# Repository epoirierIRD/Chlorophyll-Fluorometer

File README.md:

<details>
<summary>⚠️ <strong>Latest News & Important Warnings</strong></summary>

### 📰 Latest News
- **06-05-2026:** Fluorometer has been successfully replicated by Jose Lopez ("pepe Tonio") in La Paz, Mexico during PSF Tempo workshop: Arturo, F. Colas, J. Flye Ste Marie, M. Gomez, E. Kraffe, R Martinez Riccon, M. Perez,  E. Poirier
- **30-04-2026:** Original PVC casing now replaced by 90mm diameter acrylic transparent casing
- **06-02-2026:** Branch https://github.com/epoirierIRD/Chlorophyll-Fluorometer/tree/main is ahead original
repository https://github.com/EnssatPhotonicsProjects/Chlorophyll-Fluorometer (not maintained)
- **14-12-2025:** Fluorometer has been successfully replicated by E. Poirier based on this repo.

### 🚨 Warnings
- This project is a student based innovation. It is now under development in research institutes, replicate with caution
- The fluorometer has not yet been validated in situ for Chla measurements. It has proven great results in laboratory under artifical light but not validated in situ
- It is not recommended to build it to have accurate measures of Chl a in situ

### ✅ Recommended Actions
- Report issues if you encounter mistakes, errors, lacks, etc... in this documentation

> ⚠️ **Disclaimer**
>
> This project is provided **as-is** for research and development purposes only.
> The authors make no guarantees regarding correctness, reliability, or fitness for any particular application.
> Use of this DIY instrument is entirely **at your own risk**.
</details>

# Chlorophyll-Fluorometer

## Description

This project aims to develop a portable and low-cost fluorometer for detecting chlorophyll-a concentration,
 a key indicator of phytoplankton presence. The project is conducted by students in photonics from Enssat in
  collaboration with the European Institute for Marine Studies (IUEM) and is part of an open-source initiative 
  to facilitate easy and cost-effective replication of the device.

This GitHub repository contains all the necessary resources and instructions for making the device.

The document [Fluoremeter overview](Fluorometer_overview.pdf) aims to provide an overview of the technical aspects of our fluorometer.

## Features

- Measures chlorophyll-a concentration in the range of [1-50] µg/L.
- Low-cost (approximately $200), low-tech, and open-source design.
- Portable

## Principle of fluorometry

The principle of fluorometry is based on the fact that chlorophyll-a in phytoplankton, when excited by a blue light source at
 a wavelength of 430 nm, re-emits light in the red spectrum around 670 nm. This red fluorescence is detected by a photodetector, 
 enabling the measurement of chlorophyll-a concentration in the sample.

## Functionality

With our setup, high sensitivity is achieved by usind two LEDs and a large-area photodiode to collect more efficiently fluorescence. 
A red filter is used to prevent the detection of wavelengths other than red. The Arduino board enables modulation and demodulation to
 eliminate ambient red light.

## Components

The main components are:

| Component | Description |
|-----------|-------------|
| LED | Light Emitting Diode for blue excitation |
| Photodiode | Detects red fluorescence |
| Arduino | Microcontroller for processing |
| ADC | Analog to Digital Converter |
| Transistor | For LED power supply |
| Amplifier | For signal enhancement|
| OLED Screen | Displays values |
| SD Card Shield | Saves values in an SD Card |

For a detailed list of components with the references, please refer to the [Components List](hardware/components.md).

## Construction of the fluorometer

### Prerequisites

- Arduino IDE
- Electronic components
- 3D printer
- Soldering equipment
- Laser cutter

### Installation Steps

1. **Clone the Repository:**

   ```bash
   git clone https://github.com/EnssatPhotonicsProjects/Chlorophyll-Fluorometer.git
   ```

### Assembling the fluorometer

Follow the steps of the [assembly guide](assembly_guide.md) to build the fluorometer.

## Avenues for Improvement

- The photodiode becomes saturated when used outdoors in bright light.
- The PVC box may not withstand high pressure underwater.

Contributions are welcomed to improve these points.

## To contribute

Contributions to this project are welcomed. Follow this procedure contribute:

1. **Fork the repository** and create your branch:

   ```bash
   git checkout -b my-new-feature
   ```

2. **Make your changes** and test them thoroughly.

3. **Document your changes** in the [EXTERNAL_CONTRIBUTIONS](EXTERNAL_CONTRIBUTIONS.md) file. Begin the file with your name, location and date.

4. **Submit a Pull Request** with a detailed description of your changes.

## Contributors

Team 2024-2025 :
- Loïc Goumarre (minimadcap)
- Cécile Plaçais (CecileP28)
- Agathe Douissard (Douidoui2)
- Olivier Josephiak (Josephiak)
- Mayssame Ismael (Goulgoul1)
- Hugo Le Moal (HugoLeMoal)
- Viken Tevonian
- Merlin Rivière

Team 2023-2024 :
- Jérémy Gigandet
- Brice Hervé
- Thomas Quinchon
- Damien Depauw
- Etienne Chaillot
- Nicolas Chabrier
- Thomas Gysemberg

## Acknowledgments

The authors warmly thank Thierry Chartier, Laurent Bramerie, supervisors of the project at Enssat, Philippe Laborie (Laboratoire de physique corpusculaire, Caen, France) and Etienne Poirier (IUEM, Plouzané, France), members of the steering committee, for their advice and support throughout the project. Special thanks to Etienne Poirier for giving the idea of the project, trusting us and welcome us at IUEM in the last days of the project.

Authors are also very grateful to Antoine Courtay, Hervé Daniel, Clément Dauphin, Hervé Chuberre, teachers at Enssat, and Jean-Philippe Lesault, technician at Enssat, for their advice and technical support. Special thanks to Yvan Guilloit, in charge of the MakerSpace at IUT de Lannion, France, for his help in the integration of the device in the waterproof box.

The fluorometer project started in september 2023 with a first team of Enssat students. Our fluorometer could not have been finalized without their initial work. Many thanks to Nicolas Chabrier, Etienne Chaillot, Damien Depauw, Jérémy Gigandet, Thomas Gysemberg, Brice Hervé, and Thomas Quinchon.

We had the chance to meet Michel Hignette (oceanographer and president of ArmorScience, Lannion, France). We are very grateful to him for sharing his knowledge on phytoplankton.

Hence, we would like to thank Maël Guibré (student at IUT de Lannion) for the time he took to make some videos of the project.

## License

This project is licensed under [CC BY-SA 4.0]. Please see the [`LICENSE`](LICENSE.md) file for more details.

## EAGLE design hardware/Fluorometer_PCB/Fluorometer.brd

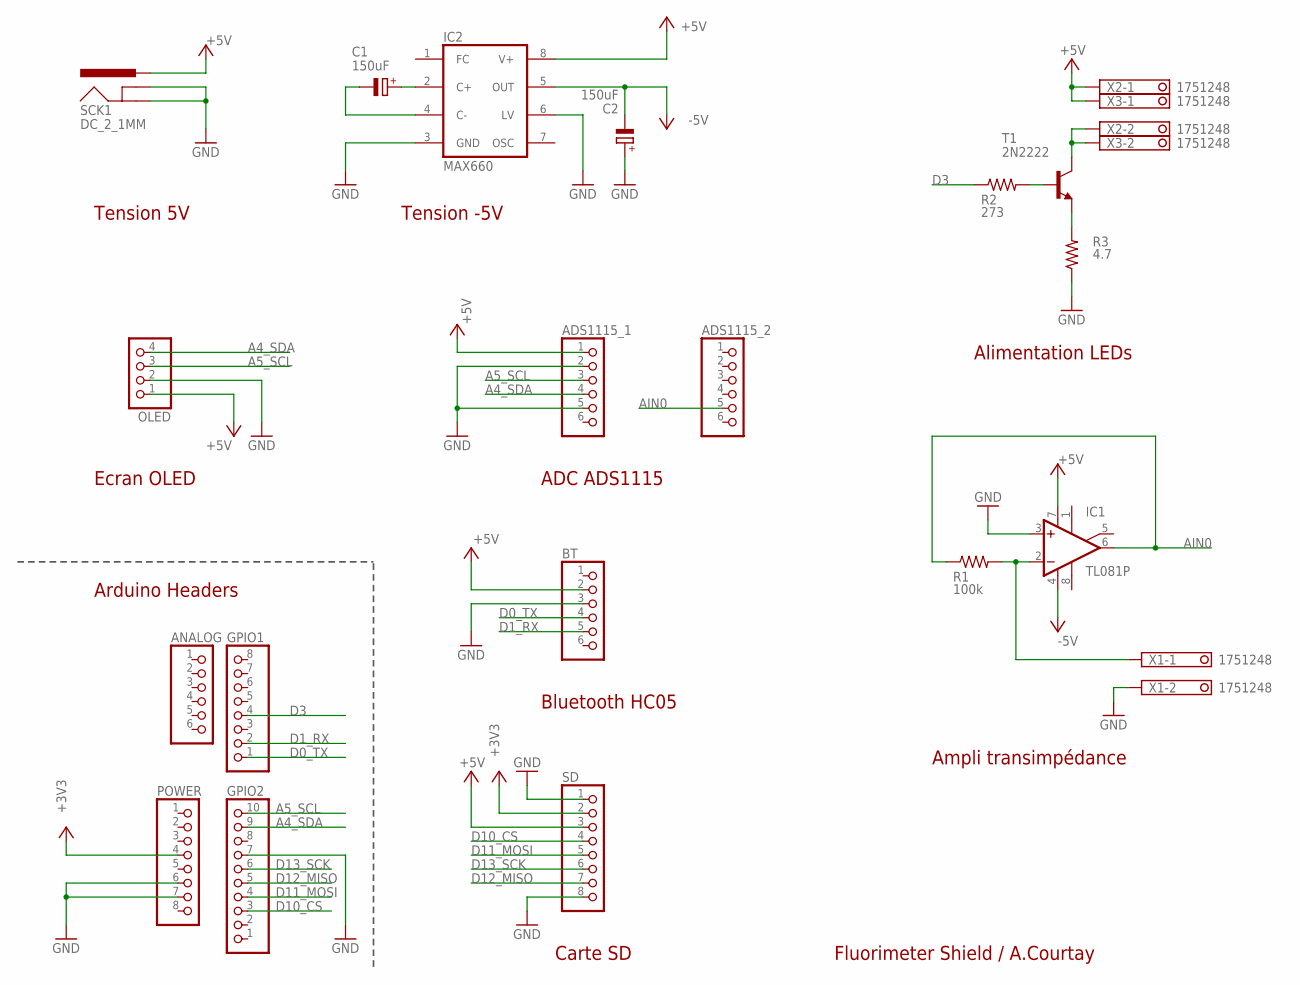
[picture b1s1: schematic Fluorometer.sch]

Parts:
ADS1115_1, ADS1115_2: PINHD-1X6; 1X06
ANALOG: PINHD-1X6; 1X06
BT: PINHD-1X6; 1X06
C1, C2: 150uF; E2,5-7
GPIO1: PINHD-1X8; 1X08
GPIO2: PINHD-1X10; 1X10
IC1: TL081P; DIL08
IC2: MAX660; DIL08
OLED: PINHD-1X4; 1X04
POWER: PINHD-1X8; 1X08
R1: 100k; 0204/7
R2: 273; 0204/7
R3: 4.7; 0204/7
SCK1: DC_2_1MM; POWER_JACK_PTH
SD: PINHD-1X8; 1X08
T1: 2N2222; TO18
X1, X2, X3: 1751248

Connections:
+3V3: POWER.4, SD.2
+5V: ADS1115_1.1, BT.2, IC1.7 (V+), IC2.8 (V+), OLED.1, SCK1.PWR, SD.3, X2.1, X3.1
-5V: C2.-, IC1.4 (V-), IC2.5 (OUT)
A4_SDA: ADS1115_1.4, GPIO2.9, OLED.4
A5_SCL: ADS1115_1.3, GPIO2.10, OLED.3
AIN0: ADS1115_2.5, IC1.6 (OUT), R1.1
D0_TX: BT.4, GPIO1.1
D1_RX: BT.5, GPIO1.2
D3: GPIO1.4, R2.1
D10_CS: GPIO2.3, SD.4
D11_MOSI: GPIO2.4, SD.5
D12_MISO: GPIO2.5, SD.7
D13_SCK: GPIO2.6, SD.6
GND: ADS1115_1.2, ADS1115_1.5, BT.3, C2.+, GPIO2.7, IC1.3 (+IN), IC2.3 (GND), IC2.6 (LV), OLED.2, POWER.6, POWER.7, R3.1, SCK1.GND, SCK1.GNDBREAK, SD.1, SD.8, X1.2
unnamed: IC1.2 (-IN), R1.2, X1.1
unnamed: R2.2, T1.2 (B)
unnamed: R3.2, T1.1 (E)
unnamed: T1.3 (C), X2.2, X3.2
unnamed: C1.+, IC2.2 (C+)
unnamed: C1.-, IC2.4 (C-)

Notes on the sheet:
Tension 5V
Ecran OLED
Ampli transimpédance
Alimentation LEDs
ADC ADS1115
Tension -5V
Arduino Headers
Bluetooth HC05
Fluorimeter Shield / A.Courtay
Carte SD

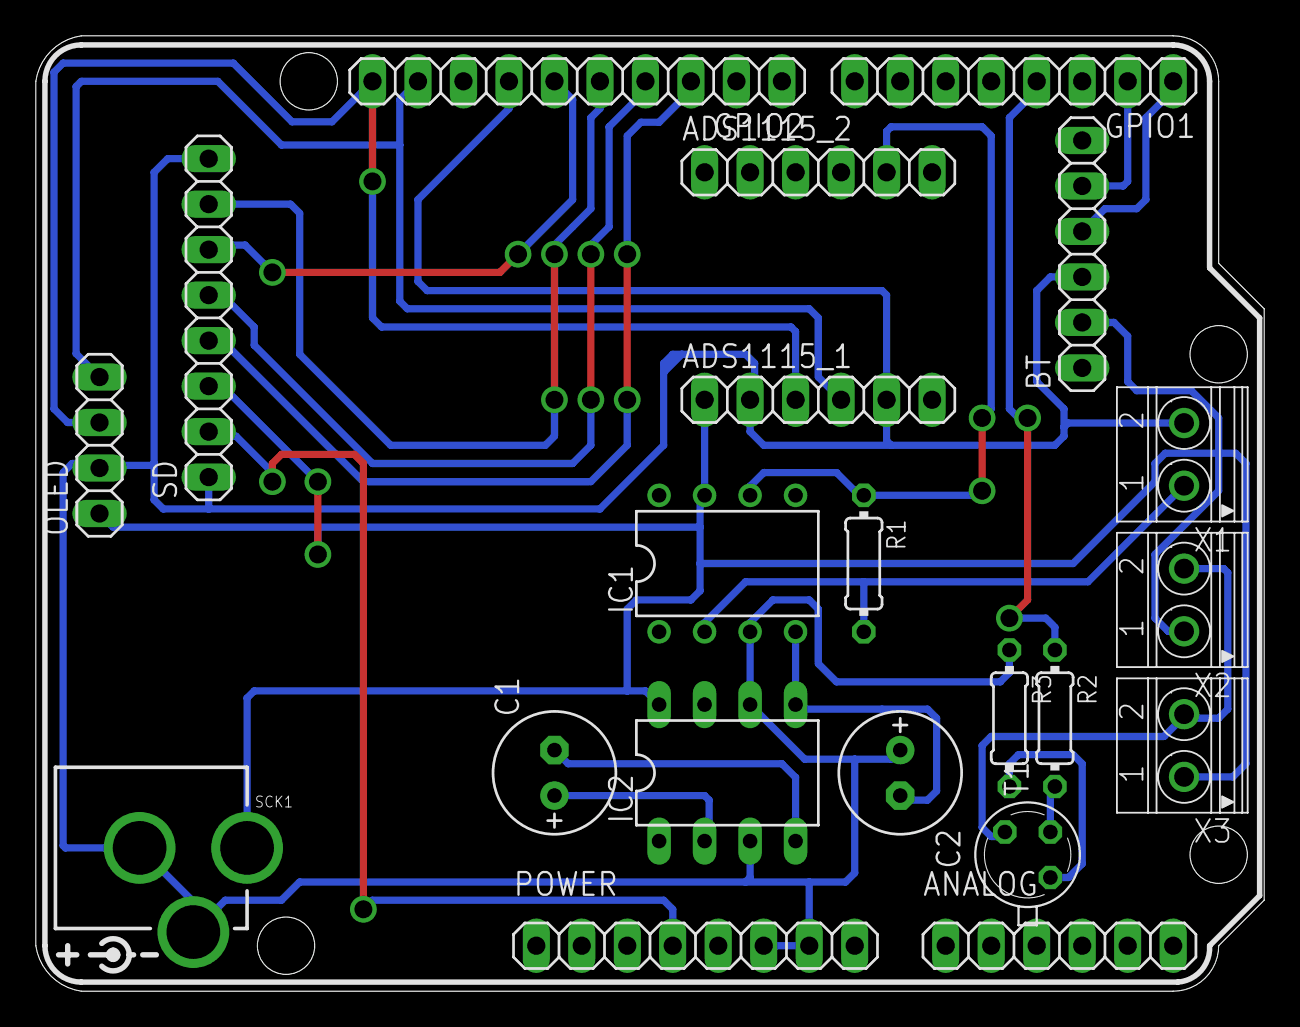
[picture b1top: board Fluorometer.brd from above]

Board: 2 copper layers, 68.6 x 53.3 mm, 21 parts (0 on the bottom side), 20 nets.

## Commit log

2025-06-12 Update documentation links and remove redundant content
    - Fixes a broken link to the PCB design file in the assembly guide.
    - Removes unused or redundant content from README.md and calibration.md.
    - Enhances clarity and maintains consistency in documentation.
2025-06-18 Create assembly_structures_guide
2025-06-18 Rename assembly_structures_guide to assembly_structures_guide.md
2025-06-27 Rename 3. sleeve.jpg to 3.sleeve.jpg
2025-07-04 Rename Schematic.pdf to Circuit-diagram.pdf
2025-07-06 Rename External contributions.md to EXTERNAL_CONTRIBUTIONS.md
2025-07-17 updated components.md with resellers references
2025-10-03 updated components list + image with A.Courtay shield
2025-10-03 removed unused files before pull request
2025-10-06 updated components with Farnell ref from A.Courtay
2025-10-06 updated assembly guide with PCB manufacturer info
2025-11-06 updated capacitor ref in components list
2026-02-06 updated psb assembly
2026-02-06 updated assembly guide
2026-04-08 fix:调整OLED引脚避免与USB连接器接触冲突#3
    将OLED的I2C引脚从默认A4/A5改为A2/A3，解决与USB连接器的物理接触冲突问题。
2026-04-22 added pcb assembly manual + pictures
2026-04-22 updated manuals
2026-05-12 big update
2026-06-24 added Adafruit ADS1X15 to the list of required dependencies
2026-06-24 turn currents.txt into a CSV file
2026-06-25 updated supprt pcb freecad file
2026-06-26 updated PCB freecad drawing with sd card holes
2026-06-26 Add min/max values of sample to CSV file
2026-06-26 Fix computation of rolling average
2026-06-26 Make display optional
